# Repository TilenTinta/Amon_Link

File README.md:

# Amon Link

USB-powered RF bridge between **Amon Ground Control** (PC) and the **Amon Lander** drone, built around the WCH **CH32V003F4P6** MCU with **dual NRF24L01 + RFX2401C** radios for robust range. 

> Part of the Amon Lander project:
>
> - **Amon Lander** — overall vehicle, frame, test/control SW, and data  
>   https://github.com/TilenTinta/Amon_Lander
> - **Amon Board** — flight controller hardware & firmware  
>   https://github.com/TilenTinta/Amon_Board
> - **Amon Ground Control** — desktop GCS for telemetry & control  
>   https://github.com/TilenTinta/Amon_GroundControl_Software

---

## Table of Contents

- [Overview](#overview)
- [Features](#features)
  - [Hardware](#hardware)
  - [Software & Compatibility](#software--compatibility)
  - [Diagnostics & Controls](#diagnostics--controls)
- [Quick Start](#quick-start)
- [Flashing Firmware](#flashing-firmware)
- [Debugging](#debugging)
  - [LED Status Codes](#led-status-codes)
  - [Button Usage](#button-usage)
- [Repository Structure](#repository-structure)
- [Roadmap](#roadmap)
- [Status & Disclaimer](#status--disclaimer)
- [License](#license)
- [Acknowledgments](#acknowledgments)

---

## Overview

**Amon Link** is a compact, low-power **RF communication bridge** that connects a PC-based Ground Control application to the Amon Lander over 2.4 GHz radios. It prioritizes reliability by pairing **two NRF24L01 modules** with the **RFX2401C PA/LNA** front-end for extended range and improved link quality. The board is powered from **USB Type‑C** and integrates a **3.3 V LDO**. 

---

## Features

### Hardware

- **MCU:** WCH **CH32V003F4P6**. 
- **Power:** USB‑powered with onboard **3.3 V LDO**. 
- **Connector:** **USB Type‑C**. 
- **RF Link:** Dual **NRF24L01** radios with **RFX2401C (PA+LNA)** for long range and better SNR. 
- **Indicators/Controls:** Status LED and button for reconnect/SW update. 

### Software & Compatibility

- **Firmware:** C, developed in **MounRiver Studio IDE**. 
- **USB–UART:** **CH340G** bridge (install drivers if needed). 
- **Platforms:** Works with **Windows, Linux, and macOS** Ground Control apps. 
- **Updates:** **Custom bootloader** supports USB firmware updates. 

### Diagnostics & Controls

- **Status LED** for connection state. 
- **Button** to trigger manual reconnect and entering bootloader mode. 

---

## Quick Start

1. **Connect** the Amon Link board to your PC using **USB‑C**.   
2. **Install drivers** if required for **CH340G**.   
3. **Place antennas** for the two NRF24L01 radios to ensure clear line‑of‑sight where possible.   
4. **Launch** the Amon Ground Control application and select the appropriate COM port.

---

## Flashing Firmware

- Open the project in **MounRiver Studio IDE**, compile, and **upload** to the **CH32V003F4P6** MCU. 

> The board also includes a **custom bootloader** for **USB firmware updates** which is supported by the desktop software. 

### Bootloader
Firmware for device also includes bootloader option. To flash that:
- First flash bootloader (folder: **Bootloader**),
- after that you can flash main **hex** file over USB and desktop app (folder: **Firmware**)

If bootloader is not used you **MUST** modify the code in folder **Firmware**. In file `Link.ld` change code on the top of the file to:

```c
/* Full flash 16KB */
__app_size = 16K;

MEMORY
{
  /* Application region - 16KB */  
	FLASH (rx) : ORIGIN = 0x00000000, LENGTH = __app_size 

  /* RAM - untouched 2KB */  
	RAM (xrw)  : ORIGIN = 0x20000000, LENGTH = 2K
}

SECTIONS
{
  .init :
  {
    ...
```
Once the bootloader is flashed, you can put your device in firmware update mode by holding the **Reconnect** button while plugging in the USB cable or by triggering it via software. When the blue and red LEDs are lights up, you're in firmware update mode!

The firmware can be updated using a graphical application. The application is built with a Python backend and an Electron front end. You can select and import either a hex or a binary file. Once imported, the CRC32 checksum is calculated for the file.

This checksum is used during device connection. When the device connects, a handshake process exchanges several pieces of data, one of which is the CRC32 value of the firmware currently installed on the device. If this CRC matches the one from the new file, you are notified before proceeding with the update. After a successful update, the new CRC32 value is written to the device for future reference.

---

## Debugging

### LED Status Codes  

| LED Pattern (App)     | Meaning                  |
|-----------------|---------------------------|
| Constant blinking **red**   | Device initialization failed |
| Solid **blue**    | Device initialized           |
| Blinking **red**     | Received packet          |

| LED Pattern (Boot)     | Meaning                   |
|-----------------|---------------------------|
| Solid **blue** and **red**    | Waiting on USB data    |

### Button Usage  

Press the **button** to trigger a manual **reconnect** attempt or befor powring up device to enter bootloader mode.

## Range testing
The plan for this device is not to reach over 1 km of range, but only a few meters are enough for now. To test this, I did a simple test. I connected the device to my laptop and established a connection from the **Ground control app** to **Amon Link** and from that to **Amon Lander**. After receiving telemetry data, I started moving away from the drone. This test was done with line of sight between the drone and link device.

Because of field limitations, the test was not done until telemetry cut-off. The test will be repeated in the future to really get the limitation of radio range.

---

## Status & Disclaimer

**In active development.** The hardware and firmware are usable, but changes are ongoing; expect rough edges as features evolve.

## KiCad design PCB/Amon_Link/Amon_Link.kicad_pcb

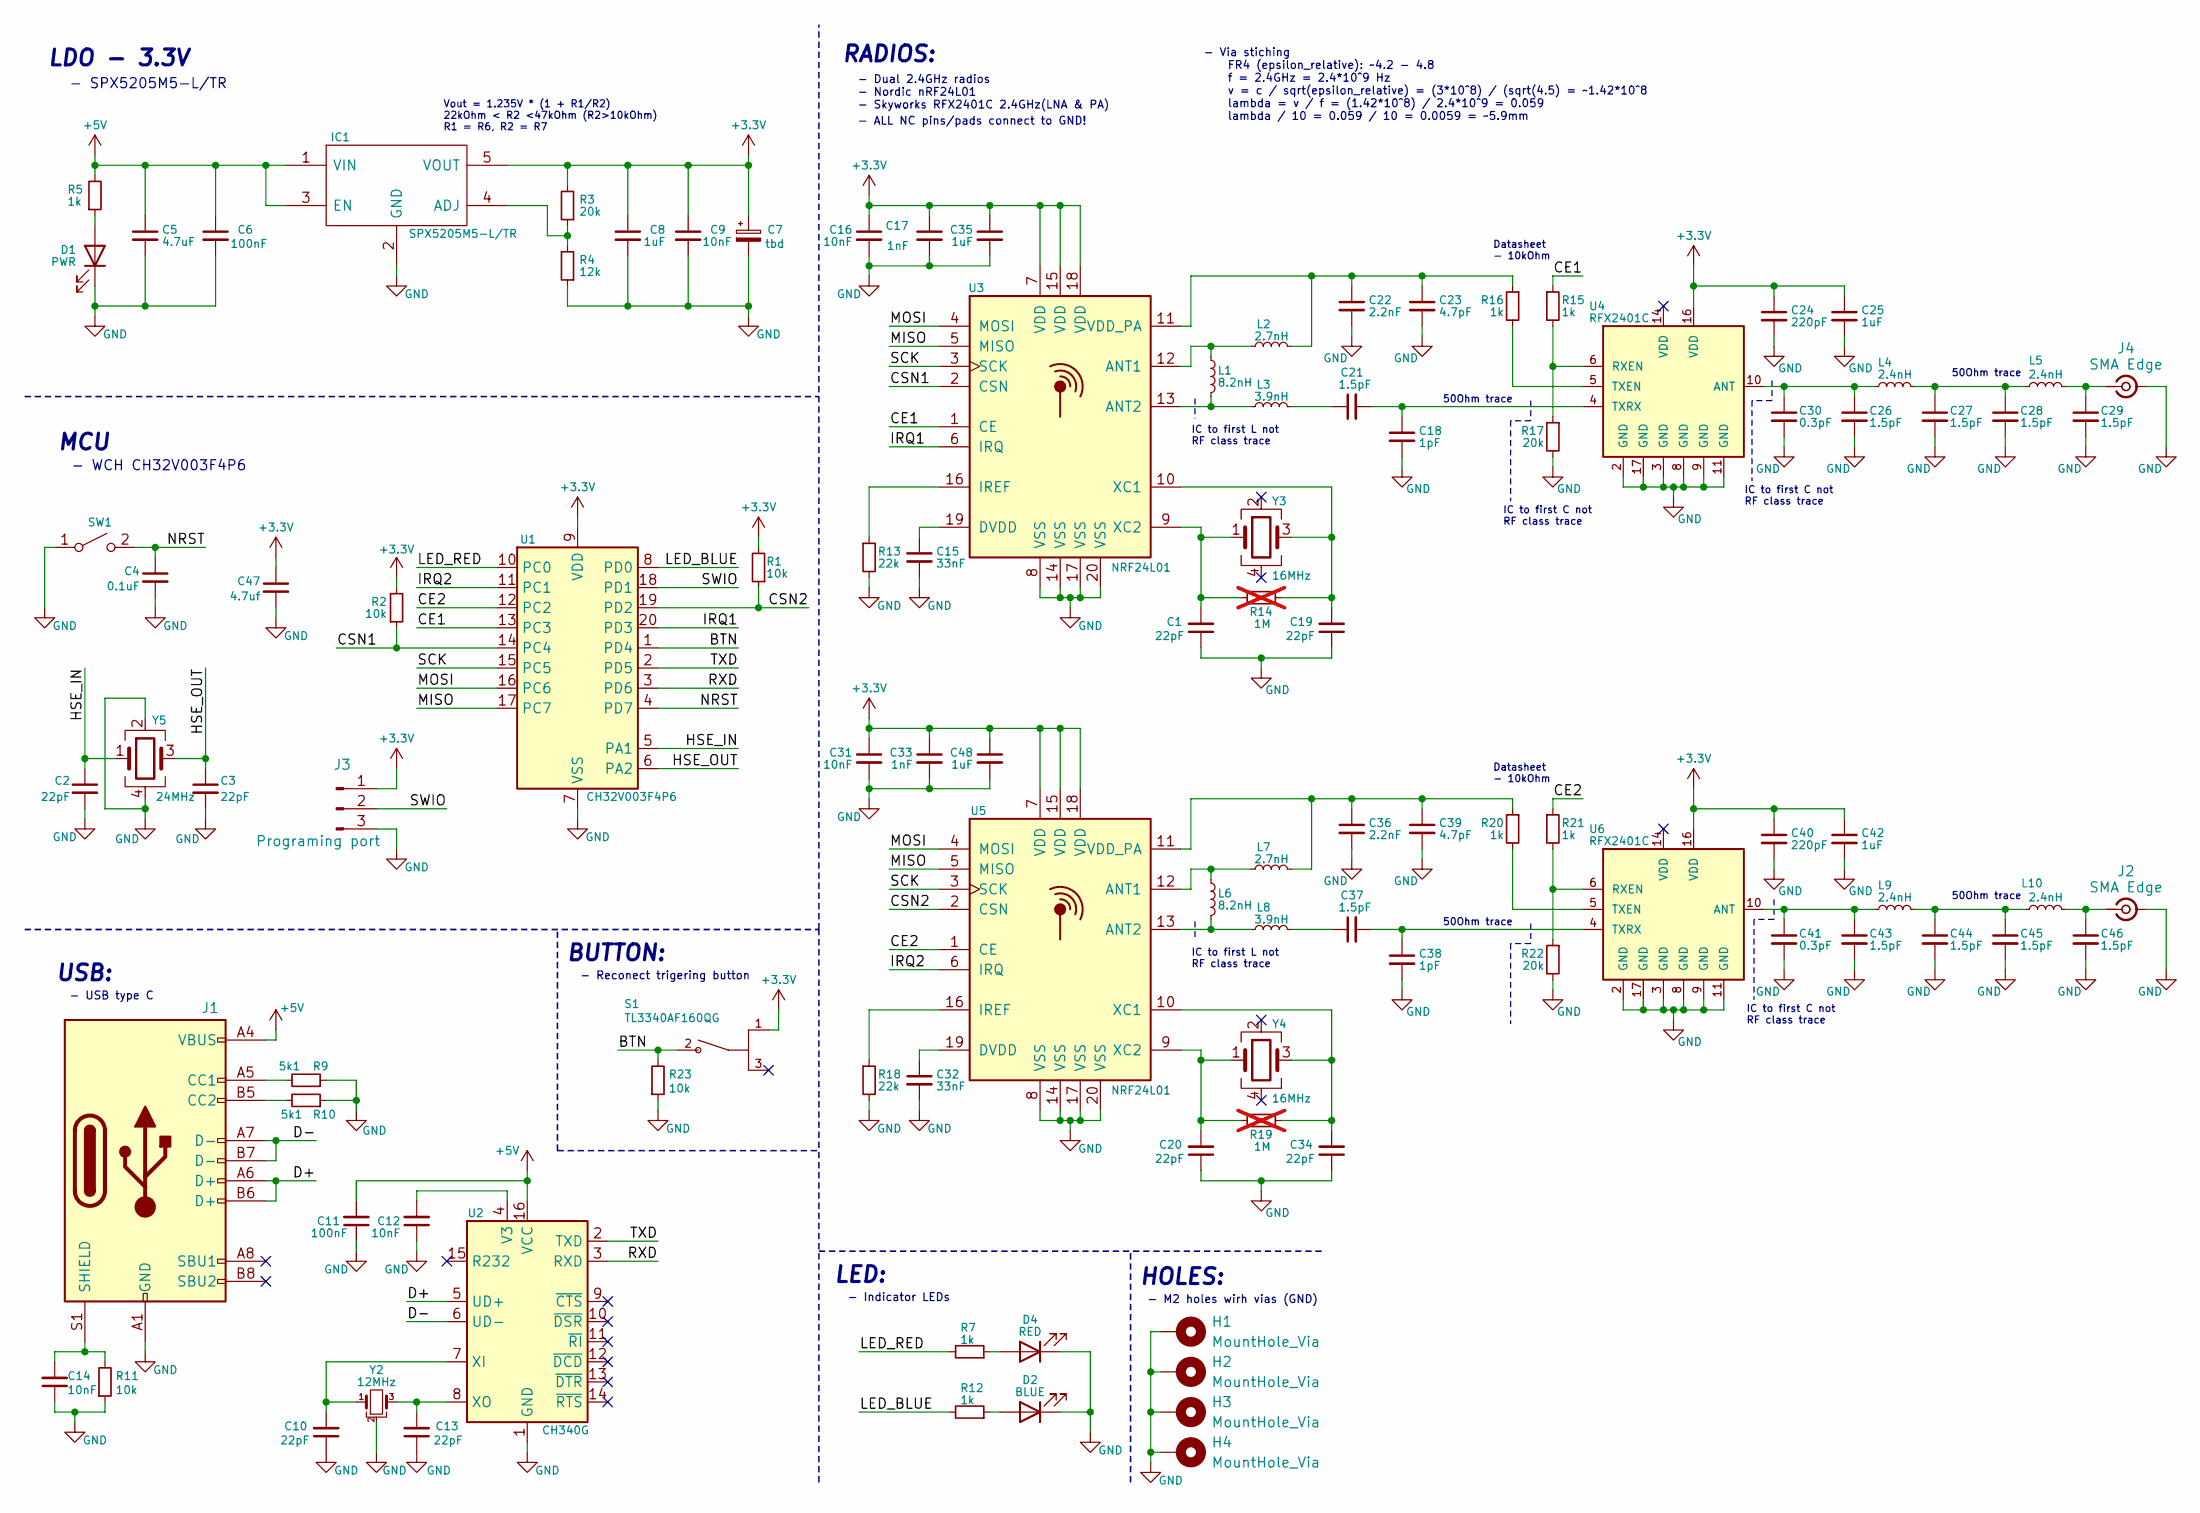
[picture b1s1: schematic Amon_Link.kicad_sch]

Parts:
C1, C2, C3, C10, C13, C19, C20, C34: 22pF; C_0402_1005Metric
C4: 0.1uF; C_0603_1608Metric
C5: 4.7uF; C_1206_3216Metric
C6, C11: 100nF; C_0603_1608Metric
C7: tbd; CP_EIA-3528-12_Kemet-T
C8: 1uF; C_0603_1608Metric
C9, C12, C14: 10nF; C_0603_1608Metric
C15, C32: 33nF; C_0402_1005Metric
C16, C31: 10nF; C_0402_1005Metric
C17, C33: 1nF; C_0402_1005Metric
C18, C38: 1pF; C_0402_1005Metric
C21, C26, C27, C28, C29, C37, C43, C44, C45, C46: 1.5pF; C_0402_1005Metric
C22, C36: 2.2nF; C_0402_1005Metric
C23, C39: 4.7pF; C_0402_1005Metric
C24, C40: 220pF; C_0402_1005Metric
C25, C35, C42, C48: 1uF; C_0402_1005Metric
C30, C41: 0.3pF; C_0402_1005Metric
C47: 4.7uf; C_0603_1608Metric
D1: PWR; LED_0603_1608Metric
D2: BLUE; LED_1206_3216Metric
D4: RED; LED_1206_3216Metric
H1, H2, H3, H4: MountHole_Via; MountingHole_2.2mm_M2_Pad_Via
IC1: SPX5205M5-L/TR; SOT95P280X145-5N; Manufacturer_Part_Number SPX5205M5-L-3-3/TR; Mouser Part Number 701-SPX5205M5-L-33TR
J1: USB_C_Receptacle_USB2.0; USB_C_Receptacle_XKB_U262-16XN-4BVC11
J2, J4: SMA Edge; SMA_Samtec_SMA-J-P-X-ST-EM1_EdgeMount
J3: Programing port; PinHeader_1x03_P2.54mm_Vertical
L1, L6: 8.2nH; L_0402_1005Metric
L2, L7: 2.7nH; L_0402_1005Metric
L3, L8: 3.9nH; L_0402_1005Metric
L4, L5, L9, L10: 2.4nH; L_0402_1005Metric
R1, R2, R11, R23: 10k; R_0603_1608Metric
R3: 20k; R_0603_1608Metric
R4: 12k; R_0603_1608Metric
R5, R7, R12: 1k; R_0603_1608Metric
R9, R10: 5k1; R_0603_1608Metric
R13, R18: 22k; R_0402_1005Metric
R14, R19: 1M; R_0402_1005Metric; not fitted
R15, R16, R20, R21: 1k; R_0402_1005Metric
R17, R22: 20k; R_0402_1005Metric
S1: TL3340AF160QG; SW_TL3340AF160QG
SW1: SW_SPST; SW_Push_1P1T_NO_CK_KMR2
U1: CH32V003F4P6; TSSOP-20_4.4x6.5mm_P0.65mm
U2: CH340G; SOIC-16_3.9x9.9mm_P1.27mm
U3, U5: NRF24L01; QFN-20-1EP_4x4mm_P0.5mm_EP2.5x2.5mm
U4, U6: RFX2401C; QFN50P300X300X60-17N
Y2: 12MHz; Resonator_SMD_Murata_CSTxExxV-3Pin_3.0x1.1mm
Y3, Y4: 16MHz; Crystal_SMD_3225-4Pin_3.2x2.5mm
Y5: 24MHz; Crystal_SMD_3225-4Pin_3.2x2.5mm

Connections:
+3.3V: C7.1, C8.1, C9.1, C16.1, C17.1, C24.1, C25.1, C31.1, C33.1, C35.1, C40.1, C42.1, C47.1, C48.1, IC1.5 (VOUT), J3.1, R1.2, R2.2, R3.2, S1.1, U1.9 (VDD), U3.7 (VDD), U3.15 (VDD), U3.18 (VDD), U4.16 (VDD), U5.7 (VDD), U5.15 (VDD), U5.18 (VDD), U6.16 (VDD)
+5V: C5.1, C6.1, C11.2, IC1.1 (VIN), IC1.3 (EN), J1.A4 (VBUS), J1.A9 (VBUS), J1.B4 (VBUS), J1.B9 (VBUS), R5.2, U2.16 (VCC)
/BTN: R23.2, S1.2, U1.1 (PD4)
/CE1: R15.1, U1.13 (PC3), U3.1 (CE)
/CE2: R21.1, U1.12 (PC2), U5.1 (CE)
/CSN1: R2.1, U1.14 (PC4), U3.2 (CSN)
/CSN2: R1.1, U1.19 (PD2), U5.2 (CSN)
/D+: J1.A6 (D+), J1.B6 (D+), U2.5 (UD+)
/D-: J1.A7 (D-), J1.B7 (D-), U2.6 (UD-)
/HSE_IN: C2.1, U1.5 (PA1), Y5.1
/HSE_OUT: C3.1, U1.6 (PA2), Y5.3
/IRQ1: U1.20 (PD3), U3.6 (IRQ)
/IRQ2: U1.11 (PC1), U5.6 (IRQ)
/LED_BLUE: R12.2, U1.8 (PD0)
/LED_RED: R7.2, U1.10 (PC0)
/MISO: U1.17 (PC7), U3.5 (MISO), U5.5 (MISO)
/MOSI: U1.16 (PC6), U3.4 (MOSI), U5.4 (MOSI)
/NRST: C4.1, SW1.2 (B), U1.4 (PD7)
/RXD: U1.3 (PD6), U2.3 (RXD)
/SCK: U1.15 (PC5), U3.3 (SCK), U5.3 (SCK)
/SWIO: J3.2, U1.18 (PD1)
/TXD: U1.2 (PD5), U2.2 (TXD)
GND: C1.1, C2.2, C3.2, C4.2, C5.2, C6.2, C7.2, C8.2, C9.2, C10.1, C11.1, C12.1, C13.1, C14.1, C15.2, C16.2, C17.2, C18.2, C19.1, C20.1, C22.2, C23.2, C24.2, C25.2, C26.2, C27.2, C28.2, C29.2, C30.2, C31.2, C32.2, C33.2, C34.1, C35.2, C36.2, C38.2, C39.2, C40.2, C41.2, C42.2, C43.2, C44.2, C45.2, C46.2, C47.2, C48.2, D1.1 (K), D2.1 (K), D4.1 (K), H1.1, H1.MP, H2.1, H2.MP, H3.1, H3.MP, H4.1, H4.MP, IC1.2 (GND), J1.A1 (GND), J1.A12 (GND), J1.B1 (GND), J1.B12 (GND), J2.2 (Ext), J3.3, J4.2 (Ext), R4.1, R9.1, R10.1, R11.1, R13.2, R17.2, R18.2, R22.2, R23.1, SW1.1 (A), U1.7 (VSS), U2.1 (GND), U3.8 (VSS), U3.14 (VSS), U3.17 (VSS), U3.20 (VSS), U4.2 (GND), U4.3 (GND), U4.8 (GND), U4.9 (GND), U4.11 (GND), U4.17 (GND), U5.8 (VSS), U5.14 (VSS), U5.17 (VSS), U5.20 (VSS), U6.2 (GND), U6.3 (GND), U6.8 (GND), U6.9 (GND), U6.11 (GND), U6.17 (GND), Y2.2, Y5.2, Y5.4
unnamed: C21.1, L3.2
unnamed: C27.1, C28.1, L4.2, L5.1
unnamed: C37.1, L8.2
unnamed: C44.1, C45.1, L9.2, L10.1
unnamed: D1.2 (A), R5.1
unnamed: D2.2 (A), R12.1
unnamed: D4.2 (A), R7.1
unnamed: IC1.4 (ADJ), R3.1, R4.2
unnamed: J1.A5 (CC1), R9.2
unnamed: J1.B5 (CC2), R10.2
unnamed: C14.2, J1.S1 (SHIELD), R11.2
unnamed: C46.1, J2.1 (In), L10.2
unnamed: C29.1, J4.1 (In), L5.2
unnamed: C12.2, U2.4 (V3)
unnamed: C10.2, U2.7 (XI), Y2.1
unnamed: C13.2, U2.8 (XO), Y2.3
unnamed: L1.1, L2.1, U3.12 (ANT1)
unnamed: L1.2, L3.1, U3.13 (ANT2)
unnamed: C15.1, U3.19 (DVDD)
unnamed: R13.1, U3.16 (IREF)
unnamed: C22.1, C23.1, L2.2, R16.1, U3.11 (VDD_PA)
unnamed: C19.2, R14.2, U3.10 (XC1), Y3.3
unnamed: C1.2, R14.1, U3.9 (XC2), Y3.1
unnamed: C26.1, C30.1, L4.1, U4.10 (ANT)
unnamed: R15.2, R17.1, U4.6 (RXEN)
unnamed: R16.2, U4.5 (TXEN)
unnamed: C18.1, C21.2, U4.4 (TXRX)
unnamed: L6.1, L7.1, U5.12 (ANT1)
unnamed: L6.2, L8.1, U5.13 (ANT2)
unnamed: C32.1, U5.19 (DVDD)
unnamed: R18.1, U5.16 (IREF)
unnamed: C36.1, C39.1, L7.2, R20.1, U5.11 (VDD_PA)
unnamed: C34.2, R19.2, U5.10 (XC1), Y4.3
unnamed: C20.2, R19.1, U5.9 (XC2), Y4.1
unnamed: C41.1, C43.1, L9.1, U6.10 (ANT)
unnamed: R21.2, R22.1, U6.6 (RXEN)
unnamed: R20.2, U6.5 (TXEN)
unnamed: C37.2, C38.1, U6.4 (TXRX)

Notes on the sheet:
IC to first C not RF class trace
Vout = 1.235V * (1 + R1/R2) 22kOhm < R2 <47kOhm (R2>10kOhm) R1 = R6, R2 = R7
BUTTON:
50Ohm trace
RADIOS:
- Reconect trigering button
- Via stiching FR4 (epsilon_relative): ~4.2 - 4.8 f = 2.4GHz = 2.4*10^9 Hz v = c / sqrt(epsilon_relative) = (3*10^8) / (sqrt(4.5) = ~1.42*10^8 lambda = v / f = (1.42*10^8) / 2.4*10^9 = 0.059 lambda / 10 = 0.059 / 10 = 0.0059 = ~5.9mm
IC to first L not RF class trace
- ALL NC pins/pads connect to GND!
- Dual 2.4GHz radios - Nordic nRF24L01 - Skyworks RFX2401C 2.4GHz(LNA & PA)
Datasheet - 10kOhm
LDO - 3.3V
- M2 holes wirh vias (GND)
USB:
- USB type C
HOLES:
- Indicator LEDs
- WCH CH32V003F4P6
MCU
LED:
- SPX5205M5-L/TR

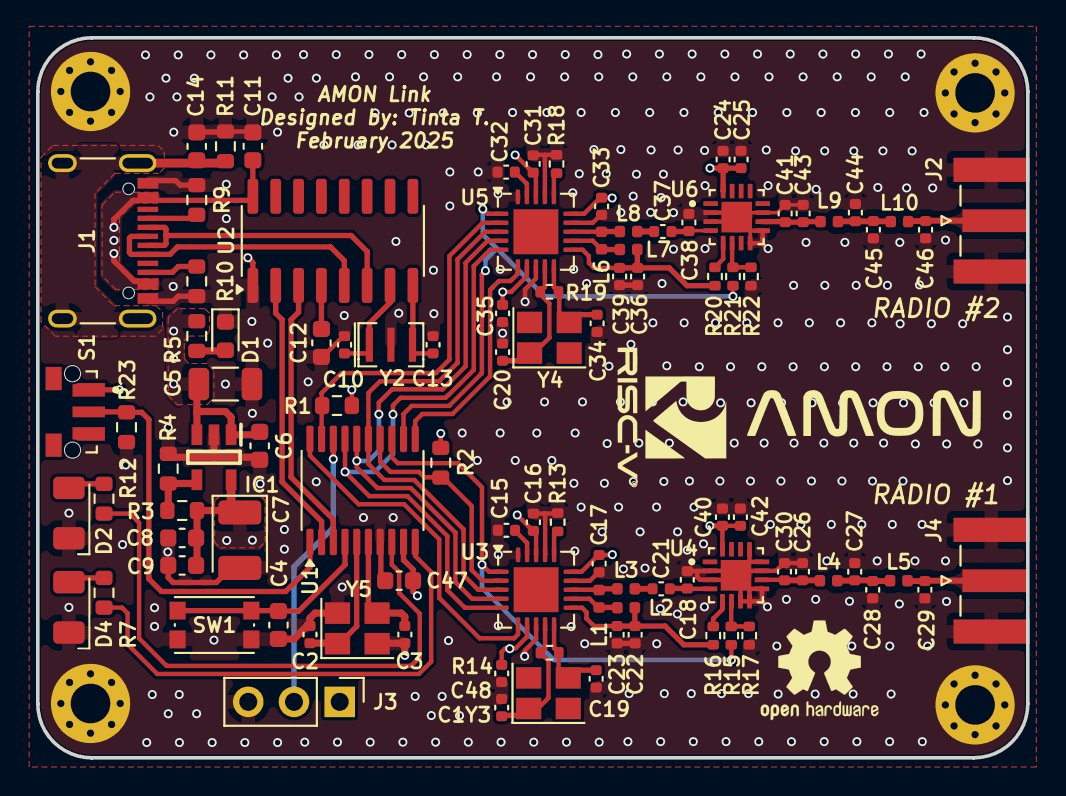
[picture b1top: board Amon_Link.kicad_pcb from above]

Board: 4 copper layers, 55.0 x 40.0 mm, 103 parts (0 on the bottom side), 61 nets.

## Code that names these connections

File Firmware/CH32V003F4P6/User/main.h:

/*****************************************************************
 * File Name          : main.h
 * Author             : Tinta T.
 * Version            : V1.0.0
 * Date               : 2025/02/11
 * Description        : Main header file of Amon Link
*****************************************************************/

#ifndef USER_MAIN_H_
#define USER_MAIN_H_

/* Includes */
#include <stdio.h>
#include <stdint.h>
#include <string.h>
#include "NRF24L01/NRF24L01.h"              // Library for radios
#include "DataTranscode/data_transcode.h"   // Encoders and decoder for data frafic
#include "device.h"                         // Helper functions for device


/*###########################################################################################################################################################*/
/* Defines */

// Device constants
#define DEVICE_NAME    "AMON Link"      // Name of the device
#define SW_VER              1           // Software version (used in UART packets)
#define SW_DATE        "February 2025"  // Date of software
#define APP_END_ADDRESS     0x08004000  // End address of flash
#define PAGE_SIZE           64          // Page size in bytes
#define APP_METADATA_ADDR   APP_END_ADDRESS - PAGE_SIZE // Address in flash where FW data is stored (flags, CRC32) - 64 Bytes

#define RADIO_NO            2           // Number of radios (1 or 2)
//#define RADIO_HW_ACK				    // Uncomment to enable use of HW ACK function provided by IC (NRF24L01) TODO

#define STATE_INIT          0           // State machine value: boot-up (blue light)
#define STATE_RUNNING       1           // State machine value: device initializet correctly, data trafic is running
#define STATE_CONN_FAIL     2           // State machine value: connect failed (red light blinking, do nothing)
#define STATE_IDLE          3           // State machine value: state where device doesnt do anything
#define STATE_FAIL          4           // State machine value: device initialization fail

#define CONN_STATUS_OK      1           // Flag that indicates the connection status - connected
#define CONN_STATUS_NOK     0           // Flag that indicates the connection status - disconnected

#define STATE_DATA_TRANSMIT 0           // State of communication where only commands and response will be transmited - changed with take off / landing
#define STATE_DATA_STREAM   1           // State of communication where drone will stream telemetry and stuf - changed with take off / landing


// Pinout
#define LED_RED             GPIO_Pin_0  // PC0: Pin of red LED
#define LED_BLUE            GPIO_Pin_0  // PD0: Pin of blue LED
#define BTN_PIN             GPIO_Pin_4  // PD4: Pin of reconnect button

#define USART_RX            GPIO_Pin_6  // PD6: USART RX pin (mistake - pin remaping)
#define USART_TX            GPIO_Pin_5  // PD5: USART TX pin (mistake - pin remaping)

#define NRF_MOSI            GPIO_Pin_6  // PC6: SPI MOSI pin for radios
#define NRF_MISO            GPIO_Pin_7  // PC7: SPI MISO pin for radios
#define NRF_SCK             GPIO_Pin_5  // PC5: SPI SCK pin for radios
#define NRF_CS1             GPIO_Pin_4  // PC4: SPI chip select pin for radio 1
#define NRF_CS2             GPIO_Pin_2  // PD2: SPI chip select pin for radio 2
#define NRF_CE1             GPIO_Pin_3  // PC3: chip enable pin for radio 1
#define NRF_CE2             GPIO_Pin_2  // PC2: chip enable pin for radio 2
#define NRF_IRQ1            GPIO_Pin_3  // PD3: interrupt pin for radio 1
#define NRF_IRQ2            GPIO_Pin_1  // PC1: interrupt pin for radio 2


/*###########################################################################################################################################################*/
/* Structs */

typedef struct{

    uint32_t    device_id;              // MCU ID number (identifying the device)
    uint8_t     version;                // Version of FW (based on protocol)
    uint8_t     init_done;              // Block the initialisation process
    volatile uint8_t     state;         // Main state machine variable
    uint8_t     err_code;               // Error code used for error report

    volatile uint8_t     conn_status;   // Flag that indicates state of connection with drone
    volatile uint8_t     conn_type;     // Type of communication - transmit/stream
    uint16_t    pct_tx_cnt;             // Send packets counter
    uint16_t    pct_rx_cnt;             // Received packets counter
    uint8_t     flag_lost_connection;   // Flag that indicates connection lost (after n of retransmitions)
    uint8_t     flag_btn_rcon;          // Flag for button triggered reconnection
    uint16_t    pct_fail_cnt;           // Counter for failed packets (calculated based on packet number - if next packet num. is not +1 -> pct_fail_cnt++)
    uint8_t     flag_data_stream;       // Flag for data stream mode (radio init change)
    uint8_t     flag_link_command_rx;   // Flag for received command targeted for link device

} s_device;


typedef struct {

    // PC -> Drone and Drone -> PC //
    uint8_t     buffer_UART[64];        // Buffer for saving USB data
    uint8_t     flag_new_uart_rx_data;  // Flag indicating a new data has arrived (packet is not complete)
    uint8_t     flag_new_uart_tx_data;  // Flag indicating a new data is ready to send
    uint8_t     flag_USB_RX_new;        // Flag for new complete USB packet (PC -> link) - start decode
    
    uint8_t     flag_new_rf_rx_data;    // Flag indicating a new data has arrived
    uint8_t     flag_new_rf_tx_data;    // Flag indicating a new data is ready to send

    uint8_t     bufferDMA_RF_UART[64];  // Unused?

} s_buffers;


typedef struct {
    
    uint8_t flags;                                  // Flags - go to main app, stay in bootloader
    //uint8_t reserved1;                            // Reserved byte 1 - paddinng/aligment
    //uint8_t reserved2;                            // Reserved byte 2 - paddinng/aligment
    //uint8_t reserved3;                            // Reserved byte 3 - paddinng/aligment
    uint32_t fw_crc32;                              // Current fw crc32 value

} s_meta_data;


typedef struct {

    SPI_TypeDef *Instance;              // SPI1
    SPI_InitTypeDef Init;               // built-in SPI struct
    
} SPI_HandleTypeDef;


/*###########################################################################################################################################################*/
/* Functions */



#endif /* USER_MAIN_H_ */

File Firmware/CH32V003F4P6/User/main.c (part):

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    if (device.init_done == 0)
    {
        // Device is alive 
        //GPIO_WriteBit(GPIOC, LED_RED, Bit_SET);             
        GPIO_WriteBit(GPIOD, LED_BLUE, Bit_SET); 

        GPIO_WriteBit(GPIOC, NRF_CE1, Bit_RESET);
        GPIO_WriteBit(GPIOC, NRF_CE2, Bit_RESET); 
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            {
                radio2.config = &radio_rx_stream_cfg;
                NRF24_init(&radio2);
                //GPIO_WriteBit(GPIOC, LED_RED, Bit_SET);
            }
        }

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                //NRF24_ReadStatus(&radio1, &status); // Clear all irqs

                // End of initialization
                GPIO_WriteBit(GPIOC, LED_RED, Bit_RESET);
                GPIO_WriteBit(GPIOD, LED_BLUE, Bit_RESET);

                // Check radio initialization
                if (radio1.radioErr == NRF_ERR_BOOT || radio2.radioErr == NRF_ERR_BOOT)
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                else
                {
                    device.state = STATE_RUNNING;       // OK... continue
                    GPIO_WriteBit(GPIOD, LED_BLUE, Bit_SET);
                }
                                                
                break;
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                                {
                                    radio2.config = &radio_rx_normal_cfg;
                                    NRF24_init(&radio2);
                                    GPIO_WriteBit(GPIOC, LED_RED, Bit_RESET);
                                }

                                NRF24_Send(&radio1);
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
                                if (device.flag_data_stream)
                                {
                                    uint8_t val = GPIO_ReadOutputDataBit(GPIOC, LED_RED);
                                    GPIO_WriteBit(GPIOC, LED_RED, (int)(!val));  
                                } 
                                else
                                {
                                    GPIO_WriteBit(GPIOC, LED_RED, Bit_RESET); 
                                }
                            }

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                                    if (data_packets.uart_packet.payload[0] == 1)
                                    {
                                        device.flag_data_stream = 1;
                                        GPIO_WriteBit(GPIOC, LED_RED, Bit_SET);
                                    }
                                    else
                                    {
                                        device.flag_data_stream = 0;
                                        GPIO_WriteBit(GPIOC, LED_RED, Bit_RESET); 
                                    }
                                    break;

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                    // Report failed connection
                    char statusLabel[] = "Connection FAILED!\r\n";
                    UartSendBuffer((uint8_t*)statusLabel, strlen(statusLabel));
                    GPIO_WriteBit(GPIOC, LED_RED, Bit_SET);                     // Indicate error
                    device.state = STATE_IDLE;                                  // Go in idle mode and wait on user response

                    break;
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    RCC_APB2PeriphClockCmd(RCC_APB2Periph_GPIOC | RCC_APB2Periph_GPIOD | RCC_APB2Periph_AFIO, ENABLE);

    // Set RED LED
    GPIO_InitStructure.GPIO_Pin = LED_RED;
    GPIO_InitStructure.GPIO_Speed = GPIO_Speed_30MHz;
    GPIO_InitStructure.GPIO_Mode = GPIO_Mode_Out_PP;
    GPIO_Init(GPIOC, &GPIO_InitStructure);

    // Set BLUE LED
    GPIO_InitStructure.GPIO_Pin = LED_BLUE;
    GPIO_InitStructure.GPIO_Speed = GPIO_Speed_30MHz;
    GPIO_InitStructure.GPIO_Mode = GPIO_Mode_Out_PP;
    GPIO_Init(GPIOD, &GPIO_InitStructure);

    // Set Button pin - pin & interrupt
    GPIO_InitStructure.GPIO_Pin = BTN_PIN;
    GPIO_InitStructure.GPIO_Speed = GPIO_Speed_30MHz;
    GPIO_InitStructure.GPIO_Mode = GPIO_Mode_IPD;
    GPIO_Init(GPIOD, &GPIO_InitStructure);
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    NVIC_InitStructure.NVIC_IRQChannelCmd = ENABLE;
    NVIC_Init(&NVIC_InitStructure);

    // Set IRQ1 (Radio interrupt pin 1)
    GPIO_InitStructure.GPIO_Pin = NRF_IRQ1;
    GPIO_InitStructure.GPIO_Speed = GPIO_Speed_30MHz;
    GPIO_InitStructure.GPIO_Mode = GPIO_Mode_IPU;
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    NVIC_InitStructure.NVIC_IRQChannelCmd = ENABLE;
    NVIC_Init(&NVIC_InitStructure);

    // Set IRQ2 (Radio interrupt pin 2)
    GPIO_InitStructure.GPIO_Pin = NRF_IRQ2;
    GPIO_InitStructure.GPIO_Speed = GPIO_Speed_30MHz;
    GPIO_InitStructure.GPIO_Mode = GPIO_Mode_IPU;
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
    RCC_APB2PeriphClockCmd(RCC_APB2Periph_GPIOD | RCC_APB2Periph_USART1 | RCC_APB2Periph_AFIO, ENABLE);

    // Pin remaping (TX=PD6, RX=PD5)
    AFIO->PCFR1 &= ~((1U << 21) | (1U << 2));  // clear USART1_RM1 (bit21) and USART1_RM (bit2)
    AFIO->PCFR1 |=  (1U << 21);                // set USART1_RM1=1, USART1_RM=0  -> 10b

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        // {
        //     device.state = STATE_CONN_START;
        //     device.flag_btn_rcon = 1;
        //     GPIO_WriteBit(GPIOC, LED_RED, Bit_RESET);
        // }

        EXTI_ClearITPendingBit(EXTI_Line4);     // Clear Flag
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        //     // Blink LED (twice per second)
        //     if (cntBlink >= 12)
        //     {
        //         GPIO_WriteBit(GPIOD, LED_BLUE, (BitAction)!GPIO_ReadOutputDataBit(GPIOD, LED_BLUE));
        //         cntBlink = 0;
        //     }

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        //         cntConnectTimeout = 0;
        //         device.state = STATE_CONN_FAIL;                                 // failed connection
        //         device.conn_status = CONN_STATUS_NOK;                           // discnnected
        //         GPIO_WriteBit(GPIOD, LED_BLUE, Bit_RESET);                      // Turn off blue LED
        //     }
        // }

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            // Fast red LED blink
            if (cntFailBlink >= 4)
            {
                GPIO_WriteBit(GPIOC, LED_RED, (BitAction)!GPIO_ReadOutputDataBit(GPIOC, LED_RED));
                cntFailBlink = 0;
            }
        }
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
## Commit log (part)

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2024-01-10 First commit, case, pcb on purfboardu, FW without SPI
2024-01-10 Readme update
2025-02-15 AVR to RISC-V
2025-02-15 Readme
2025-02-17 shematic done, layout in progress
2025-02-17 pcb update and case
2025-03-09 PCB: added graphics, Firmware: USART IRQ working, pinout set
2025-08-20 Update
    PCB v0.1 complete, firmware in progress
2025-08-23 Update
    code update - leds, button, connect states, timers
2025-08-24 Update
    IRQ flags correction, pin remaping for UART, working USB communication, SPI configured, both radios has connection with mcu
2025-08-30 Update
    readme
2025-10-12 update
    usb-uart
2025-10-26 Bootloder
    Basic button bootloader routine with no firmware update implementation
2025-10-26 Updated README
    added bootloader text
2025-10-26 Update
    main Firmware settings allow debugging with bootloader flash shift
2025-11-08 Update
    bootloader progres, untested
2025-11-09 Update
    modified bootloader jump function to be RISC-V compatible, added firmware update sequence but not tested
2025-11-23 Update
    Receiving commands with CRC calculaton from PC
2025-12-25 Update
    Terminl app to GUI app (Python + Electron)
2025-12-25 Update
    Terminal app to GUI app (Python + Electron)
2025-12-27 Update
    complete bootloader code, but not tested!
2025-12-28 Update
    complete bootloader code and graphical software, tested!
2025-12-29 Update
    bootloader code cleanup
2025-12-29 Update
    added gui update report, reset option from main application on device
2026-01-04 Update
    changes to PC application. Now can enter main app withoup update
2026-01-11 Update
    nRF25L01 driver complete, untested
2026-01-14 Update
    nRF25L01 driver complete, tested, data encoding_decoding
2026-01-17 Update - CHECKPOINT
    some code changes
2026-01-21 Update
    radio parameter tune
2026-01-24 Update
    new states
2026-01-24 Update
    radio driver send timeout
2026-01-28 Update
    data stream optimization
2026-02-02 Update
    power stability optimization on PCB - added Cs for TX event
2026-02-04 Update
    readme update
2026-03-07 Update
    Added flags
2026-03-08 Update
    added TVL and OPT flags
2026-04-05 Images
2026-06-14 Bugfix: alowing short ACK messages
2026-06-19 Update: radio hw ack build flag
